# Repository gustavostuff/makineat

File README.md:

MakiNeat is a cartridge-based portable arcade tabletop. The name comes from _maquinita_, a Mexican word for arcade machines (pronounced very similarly). The display is four 8x8 LED matrices in a 16x16 field, plus eight 7-segment digits. Graphics are 1-bit (LEDs are either ON or OFF).

On a similar spirit as the Magnavox Odyssey and the Vectrex, MakiNeat uses colored, translucent sheets to cover the screen. So the overlay is an extension of the cartridge, part of the game experience. Read [overlays](docs/overlays.md) and [design](docs/design.md) for details.

An 8-bit MCU on the cartridge (AVR128DB28) runs the game and holds the picture. That is, the cartridge is both the system brain and the game data. Five MAX7219 ICs share one SPI chain to form the 16x16 LED grid. The fifth one drives the 7-segment status digits.

Simple graphics and simple controllers can still be fun. A stick (and sometimes a button) is all that's needed. Together with cartridges, colored overlays, and a sturdy design, that is the spirit of MakiNeat.

## PCBs

Copper tracing is mostly done, but not tested IRL yet. The full [SKiDL netlist](tools/kicad/main-pcb/skidl/makineat.py) and KiCad files are under `tools/kicad/main-pcb/` and `tools/kicad/cart-pcb/` (not tested IRL).

Main system PCB, 100x100 mm:

Cartridge PCB, 44x37 mm:

## Game simulator

`tools/sim` is a netlist simulation of the system. The simulator compiles the cartridge's C game code natively on the host to drive the hardware model. This same C code can be directly flashed to the AVR on the cartridge. Acetate overlays can be built in real time and are saved per game.

SKiDL export writes `tools/kicad/main-pcb/skidl/makineat.net` and updates net classes in the main-board `*.kicad_pro` files. See [design](docs/design.md) and [firmware](docs/firmware.md).

`./sim.sh` opens the UI. The active cart is named in `cart_placed.json`. Game SDK tiers (frame, map, entity, collide) are documented in [firmware](docs/firmware.md).

## 7-segment font

`tools/seven-seg-font` edits the shared 7-segment font. Each row is a symbol and the segments that light for it. Games use that table when they draw their own digits, such as the Pong title screen. Closing the editor writes `tools/fw/seven_seg_font.json` and refreshes the glyph table in `tools/fw/seven_seg_font_table.h`.

`./seven-seg-editor.sh` opens the editor.

## Design

The image below is an **AI-generated** concept idea of how the build _might_ look when assembled. It's currently only being used as a reference.

## Docs

- [Design](docs/design.md) is the system netlist, cart edge, display chain, audio wiring, and PCB layout status.
- [Firmware](docs/firmware.md) is the game loop, inputs, sound, SDK, and simulator.
- [PCB routing considerations](docs/pcb-considerations.md) is noise isolation, ground via stitching, and trace pairing rules for the main and cart layouts.
- [Test points and status LEDs](docs/test-points-and-status-leds.md) is the main-board bring-up pads and indicator LEDs in the SKiDL netlist, for placement on `makineat_v_07.kicad_pcb`.
- [Overlays](docs/overlays.md) covers physical sheets, simulator tinting, and edit controls.
- [Future plans](docs/future-plans.md) is the hardware and firmware enhancement roadmap.
- [Status digits](docs/status-digits.md) is the fifth MAX7219 driver, J7/J9 interfaces, and the planned digit daughterboard.
- [Driver to matrix pinout](docs/driver_to_matrix_pinout.md) is the MAX7219 and 1088AW LED matrix pinout and activation reference.

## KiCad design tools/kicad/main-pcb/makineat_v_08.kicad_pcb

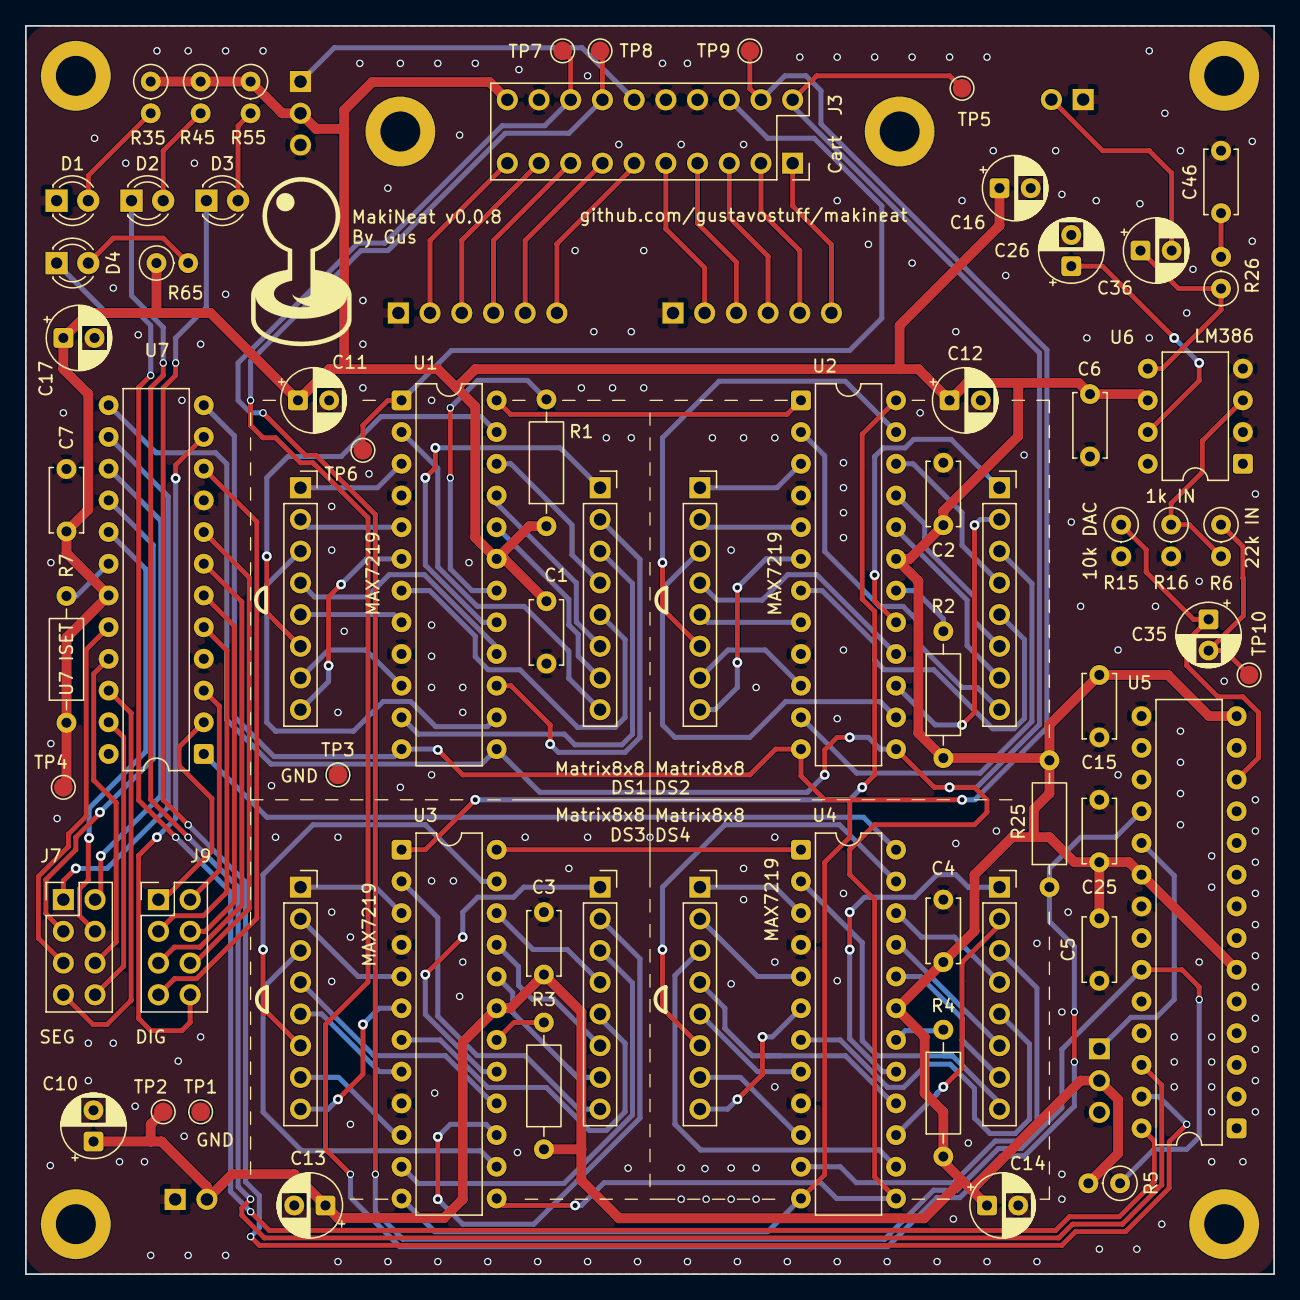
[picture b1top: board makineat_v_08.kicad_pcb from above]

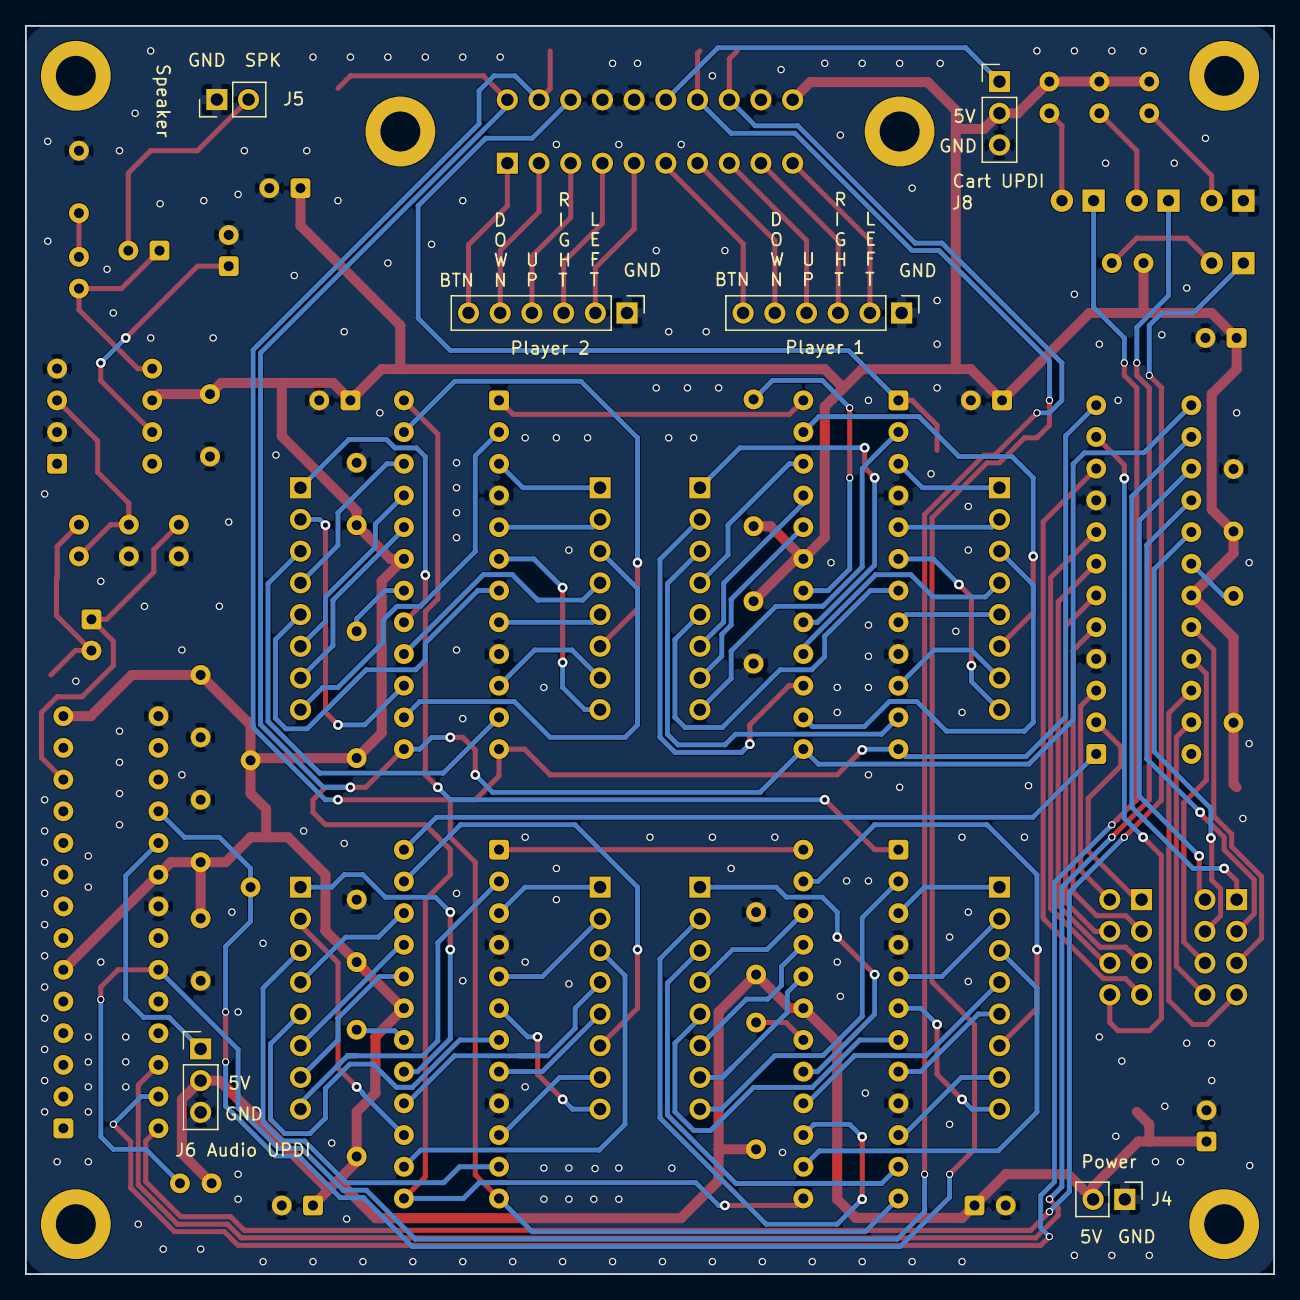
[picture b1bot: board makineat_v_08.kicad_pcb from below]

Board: 2 copper layers, 100.0 x 100.0 mm, 69 parts (6 on the bottom side), 122 nets.

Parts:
C1: U1 V+; C_Disc_D5.0mm_W2.5mm_P5.00mm
C2: U2 V+; C_Disc_D5.0mm_W2.5mm_P5.00mm
C3: U3 V+; C_Disc_D5.0mm_W2.5mm_P5.00mm
C4: U4 V+; C_Disc_D5.0mm_W2.5mm_P5.00mm
C5: U5 VDD; C_Disc_D5.0mm_W2.5mm_P5.00mm
C6: U6 VS; C_Disc_D5.0mm_W2.5mm_P5.00mm
C7: U7 V+; C_Disc_D5.0mm_W2.5mm_P5.00mm
C10: 470u VCC; CP_Radial_D5.0mm_P2.50mm
C11: U1 10u; CP_Radial_D5.0mm_P2.50mm
C12: U2 10u; CP_Radial_D5.0mm_P2.50mm
C13: U3 10u; CP_Radial_D5.0mm_P2.50mm
C14: U4 10u; CP_Radial_D5.0mm_P2.50mm
C15: U5 AVDD; C_Disc_D5.0mm_W2.5mm_P5.00mm
C16: U6 VS; CP_Radial_D5.0mm_P2.50mm
C17: U7 10u; CP_Radial_D5.0mm_P2.50mm
C25: U5 IO; C_Disc_D5.0mm_W2.5mm_P5.00mm
C26: U6 BYP; CP_Radial_D5.0mm_P2.50mm
C35: 1u DAC; CP_Radial_D5.0mm_P2.50mm
C36: 220u SPK; CP_Radial_D5.0mm_P2.50mm
C46: 47n ZOB; C_Disc_D5.0mm_W2.5mm_P5.00mm
D1: Blue Power; LED_D3.0mm_Blue
D2: Green OK; LED_D3.0mm_Green
D3: Amber Link; LED_D3.0mm_Yellow
D4: Red Fault; LED_D3.0mm_Red
DS1, DS2, DS3, DS4: Matrix8x8; Matrix8x8_2x8_P2.52mm_R25mm
J1: P1 Controls; PinHeader_1x06_P2.54mm_Vertical
J2: P2 Controls; PinHeader_1x06_P2.54mm_Vertical
J3: Cart; EDAC_395_MoboSocket_2x10_2.54x5.08mm
J4: Power; PinHeader_1x02_P2.54mm_Vertical
J5: Speaker; PinHeader_1x02_P2.54mm_Vertical
J6: Audio UPDI; PinHeader_1x03_P2.54mm_Vertical
J7: SEG; PinHeader_2x04_P2.54mm_Vertical
J8: Cart UPDI; PinHeader_1x03_P2.54mm_Vertical
J9: DIG; PinHeader_2x04_P2.54mm_Vertical
R1: U1 ISET; R_Axial_DIN0207_L6.3mm_D2.5mm_P10.16mm_Horizontal
R2: U2 ISET; R_Axial_DIN0207_L6.3mm_D2.5mm_P10.16mm_Horizontal
R3: U3 ISET; R_Axial_DIN0207_L6.3mm_D2.5mm_P10.16mm_Horizontal
R4: U4 ISET; R_Axial_DIN0207_L6.3mm_D2.5mm_P10.16mm_Horizontal
R5: 10k EVENT; R_Axial_DIN0207_L6.3mm_D2.5mm_P2.54mm_Vertical
R6: 22k IN; R_Axial_DIN0207_L6.3mm_D2.5mm_P2.54mm_Vertical
R7: U7 ISET; R_Axial_DIN0207_L6.3mm_D2.5mm_P10.16mm_Horizontal
R15: 10k DAC; R_Axial_DIN0207_L6.3mm_D2.5mm_P2.54mm_Vertical
R16: 1k IN; R_Axial_DIN0207_L6.3mm_D2.5mm_P2.54mm_Vertical
R25: 10k RESET; R_Axial_DIN0207_L6.3mm_D2.5mm_P10.16mm_Horizontal
R26: 10R ZOB; R_Axial_DIN0207_L6.3mm_D2.5mm_P2.54mm_Vertical
R35: 1k PWR; R_Axial_DIN0207_L6.3mm_D2.5mm_P2.54mm_Vertical
R45: 1k OK; R_Axial_DIN0207_L6.3mm_D2.5mm_P2.54mm_Vertical
R55: 1k LINK; R_Axial_DIN0207_L6.3mm_D2.5mm_P2.54mm_Vertical
R65: 1k FAULT; R_Axial_DIN0207_L6.3mm_D2.5mm_P2.54mm_Vertical
TP1, TP3: GND; TestPoint_Pad_D1.5mm
TP2, TP4: +5V; TestPoint_Pad_D1.5mm
TP5: CLK; TestPoint_Pad_D1.5mm
TP6: DIN; TestPoint_Pad_D1.5mm
TP7: EVENT; TestPoint_Pad_D1.5mm
TP8: RESET; TestPoint_Pad_D1.5mm
TP9: LOAD; TestPoint_Pad_D1.5mm
TP10: AUD; TestPoint_Pad_D1.5mm
U1, U2, U3, U4, U7: MAX7219; DIP-24_W7.62mm
U5: Audio AVR; DIP-28_W7.62mm
U6: LM386; DIP-8_W7.62mm

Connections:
+5V: C1.1, C2.1, C3.1, C4.1, C5.1, C6.1, C7.1, C10.1, C11.1, C12.1, C13.1, C14.1, C15.1, C16.1, C17.1, C25.1, J3.20, J4.2, J6.2, J8.2, R1.1, R2.1, R3.1, R4.1, R5.2, R7.1, R25.2, R35.1, R45.1, R55.1, R65.1, TP2.1, TP4.1, U1.19, U2.19, U3.19, U4.19, U5.6, U5.14, U5.20, U6.6, U7.19
AMP: C36.1, R26.1, U6.5
AUD: C35.2, R6.1, TP10.1
AUDIN: R6.2, R16.1, U6.3
AUDIO_UPDI: J6.1, U5.19
BYPASS: C26.1, U6.7
CLK: J3.2, TP5.1, U1.13, U2.13, U3.13, U4.13, U7.13
D1_A: D1.2, R35.2
D2_A: D2.2, R45.2
D3_A: D3.2, R55.2
D4_A: D4.2, R65.2
DAC: C35.1, R15.1, U5.12
DIN: J3.6, TP6.1, U1.1
DOUT_U1: U1.24, U2.1
DOUT_U2: U2.24, U3.1
DOUT_U3: U3.24, U4.1
DOUT_U4: U4.24, U7.1
DS1_0: DS1.0, U1.17
DS1_1: DS1.1, U1.15
DS1_2: DS1.2, U1.11
DS1_3: DS1.3, U1.22
DS1_4: DS1.4, U1.7
DS1_5: DS1.5, U1.21
DS1_6: DS1.6, U1.20
DS1_7: DS1.7, U1.2
DS1_8: DS1.8, U1.3
DS1_9: DS1.9, U1.5
DS1_A: DS1.A, U1.14
DS1_B: DS1.B, U1.16
DS1_C: DS1.C, U1.8
DS1_D: DS1.D, U1.23
DS1_E: DS1.E, U1.10
DS1_F: DS1.F, U1.6
DS2_0: DS2.0, U2.17
DS2_1: DS2.1, U2.15
DS2_2: DS2.2, U2.11
DS2_3: DS2.3, U2.22
DS2_4: DS2.4, U2.7
DS2_5: DS2.5, U2.21
DS2_6: DS2.6, U2.20
DS2_7: DS2.7, U2.2
DS2_8: DS2.8, U2.3
DS2_9: DS2.9, U2.5
DS2_A: DS2.A, U2.14
DS2_B: DS2.B, U2.16
DS2_C: DS2.C, U2.8
DS2_D: DS2.D, U2.23
DS2_E: DS2.E, U2.10
DS2_F: DS2.F, U2.6
DS3_0: DS3.0, U3.17
DS3_1: DS3.1, U3.15
DS3_2: DS3.2, U3.11
DS3_3: DS3.3, U3.22
DS3_4: DS3.4, U3.7
DS3_5: DS3.5, U3.21
DS3_6: DS3.6, U3.20
DS3_7: DS3.7, U3.2
DS3_8: DS3.8, U3.3
DS3_9: DS3.9, U3.5
DS3_A: DS3.A, U3.14
DS3_B: DS3.B, U3.16
DS3_C: DS3.C, U3.8
DS3_D: DS3.D, U3.23
DS3_E: DS3.E, U3.10
DS3_F: DS3.F, U3.6
DS4_0: DS4.0, U4.17
DS4_1: DS4.1, U4.15
DS4_2: DS4.2, U4.11
DS4_3: DS4.3, U4.22
DS4_4: DS4.4, U4.7
DS4_5: DS4.5, U4.21
DS4_6: DS4.6, U4.20
DS4_7: DS4.7, U4.2
DS4_8: DS4.8, U4.3
DS4_9: DS4.9, U4.5
DS4_A: DS4.A, U4.14
DS4_B: DS4.B, U4.16
DS4_C: DS4.C, U4.8
DS4_D: DS4.D, U4.23
DS4_E: DS4.E, U4.10
DS4_F: DS4.F, U4.6
DS5_0: J7.4, U7.17
DS5_1: J7.2, U7.15
DS5_2: J9.8, U7.11
DS5_3: J7.7, U7.22
DS5_4: J9.5, U7.7
DS5_5: J7.6, U7.21
DS5_6: J7.5, U7.20
DS5_7: J9.1, U7.2
DS5_8: J9.2, U7.3
DS5_9: J9.3, U7.5
DS5_A: J7.1, U7.14
DS5_B: J7.3, U7.16
DS5_C: J9.6, U7.8
DS5_D: J7.8, U7.23
DS5_E: J9.7, U7.10
DS5_F: J9.4, U7.6
EVENT: J3.16, R5.1, TP7.1, U5.23
GND: C1.2, C2.2, C3.2, C4.2, C5.2, C6.2, C7.2, C10.2, C11.2, C12.2, C13.2, C14.2, C15.2, C16.2, C17.2, C25.2, C26.2, C46.2, D1.1, J1.1, J2.1, J3.8, J3.10, J3.18, J4.1, J5.1, J6.3, J8.3, R15.2, R16.2, TP1.1, TP3.1, U1.4, U1.9, U2.4, U2.9, U3.4, U3.9, U4.4, U4.9, U5.15, U5.21, U6.2, U6.4, U7.4, U7.9
LED_FAULT: D4.1, U5.28
LED_LINK: D3.1, U5.27
LED_OK: D2.1, U5.26
LOAD: J3.4, TP9.1, U1.12, U2.12, U3.12, U4.12, U7.12
P1_BTN: J1.6, J3.11
P1_DOWN: J1.5, J3.13
P1_LEFT: J1.2, J3.19
P1_RIGHT: J1.3, J3.17
P1_UP: J1.4, J3.15
P2_BTN: J2.6, J3.1
P2_DOWN: J2.5, J3.3
P2_LEFT: J2.2, J3.9
P2_RIGHT: J2.3, J3.7
P2_UP: J2.4, J3.5
RESET: J3.14, R25.1, TP8.1, U5.18
SPK: C36.2, J5.2
U1_ISET: R1.2, U1.18
U2_ISET: R2.2, U2.18
U3_ISET: R3.2, U3.18
U4_ISET: R4.2, U4.18
U7_ISET: R7.2, U7.18
UPDI: J3.12, J8.1
ZOBEL: C46.1, R26.2

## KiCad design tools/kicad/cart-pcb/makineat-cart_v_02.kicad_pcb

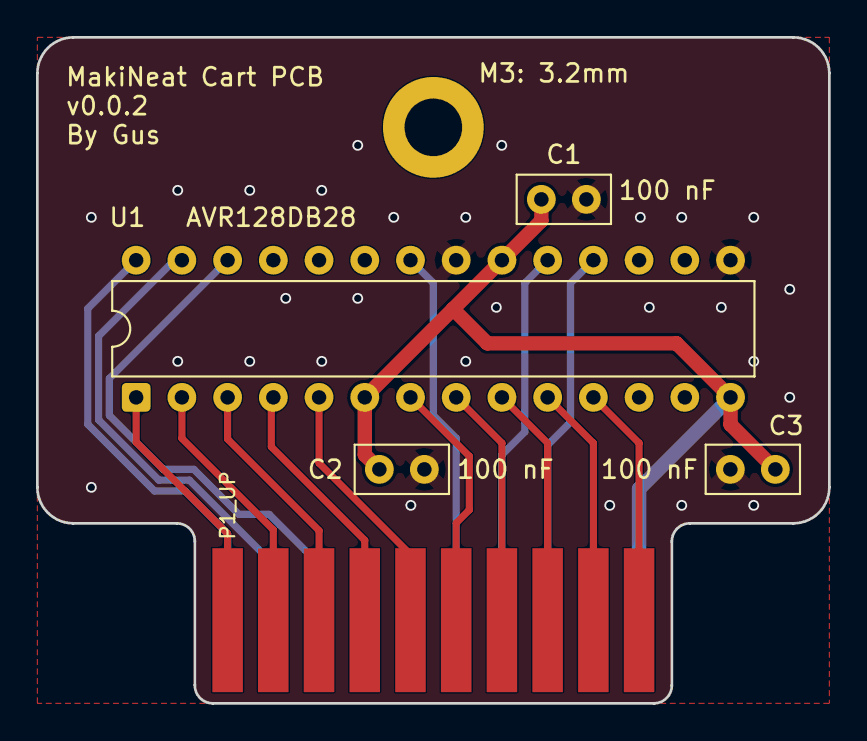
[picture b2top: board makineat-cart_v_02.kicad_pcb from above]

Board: 2 copper layers, 44.0 x 37.0 mm, 6 parts (0 on the bottom side), 18 nets.

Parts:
C1, C2, C3: 100 nF; C_Disc_D5.0mm_W2.5mm_P2.50mm
Hole: M3: 3.2mm; MountingHole_3.2mm_M3_DIN965_Pad
J1: Cart edge 2x10; Cart_Edge_2x10_P2.54mm
U1: AVR128DB28; DIP-28_W7.62mm

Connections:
+5V: C1.1, C2.1, C3.1, J1.B10, U1.6, U1.14, U1.20
CLK: J1.B1, U1.28
DIN: J1.B3, U1.26
EVENT: J1.B8, U1.18
GND: C1.2, C2.2, C3.2, J1.B4, J1.B5, J1.B9, U1.15, U1.21
LOAD: J1.B2, U1.27
P1_BTN: J1.A5, U1.5
P1_DOWN: J1.A2, U1.2
P1_LEFT: J1.A3, U1.3
P1_RIGHT: J1.A4, U1.4
P1_UP: J1.A1, U1.1
P2_BTN: J1.A10, U1.11
P2_DOWN: J1.A7, U1.8
P2_LEFT: J1.A8, U1.9
P2_RIGHT: J1.A9, U1.10
P2_UP: J1.A6, U1.7
RESET: J1.B7, U1.19
UPDI: J1.B6, U1.22

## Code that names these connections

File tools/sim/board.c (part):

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    net_tie(&board->vcc, avr_pin(&board->cpu, AVR_VDDIO2));
    net_tie(&board->gnd, avr_pin(&board->cpu, AVR_GND1));
    net_tie(&board->gnd, avr_pin(&board->cpu, AVR_GND2));
    net_tie(&board->din, avr_pin(&board->cpu, AVR_PA4));
    net_tie(&board->clk, avr_pin(&board->cpu, AVR_PA6));
    net_tie(&board->load, avr_pin(&board->cpu, AVR_PA7));
    net_tie(&board->reset, avr_pin(&board->cpu, AVR_PF6));
    net_tie(&board->updi, avr_pin(&board->cpu, AVR_UPDI));
    net_tie(&board->event, avr_pin(&board->cpu, AVR_PA0));
    net_tie(&board->event, avr_pin(&board->audio, AVR_PA1));
    net_tie(&board->vcc, avr_pin(&board->audio, AVR_VDD));
    net_tie(&board->vcc, avr_pin(&board->audio, AVR_AVDD));
    net_tie(&board->vcc, avr_pin(&board->audio, AVR_VDDIO2));
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    net_tie(&board->gnd, avr_pin(&board->audio, AVR_GND2));
    net_tie(&board->reset, avr_pin(&board->audio, AVR_PF6));

    net_tie(&board->din, max7219_pin(&board->drv[0], MAX7219_DIN));
    for (i = 0; i < NDRV; i++)
        tie_chip_rails(board, &board->drv[i]);
    for (i = 0; i < NMAT - 1; i++) {
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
